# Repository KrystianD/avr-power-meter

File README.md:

avr-power-meter
======

Device for monitoring bidirectional DC energy usage using various shunt resistors. Designed to mount directly on the shunt.

This version targets 48 V systems (supports up to 85 V on the sensing side).

It is galvanically isolated from the power supply to prevent ground loops.

It communicates via the Modbus RTU protocol over an RS-485 interface.

The core components are the `INA228` sensor and an `ATtiny1626` microcontroller.

### History

See the v1 (test) version in [[v1]](https://github.com/KrystianD/avr-power-meter/tree/v1) branch. \
See the v2 (for 24V systems) version in [[v2]](https://github.com/KrystianD/avr-power-meter/tree/v2) branch.

# Board

<br/>

# Photos

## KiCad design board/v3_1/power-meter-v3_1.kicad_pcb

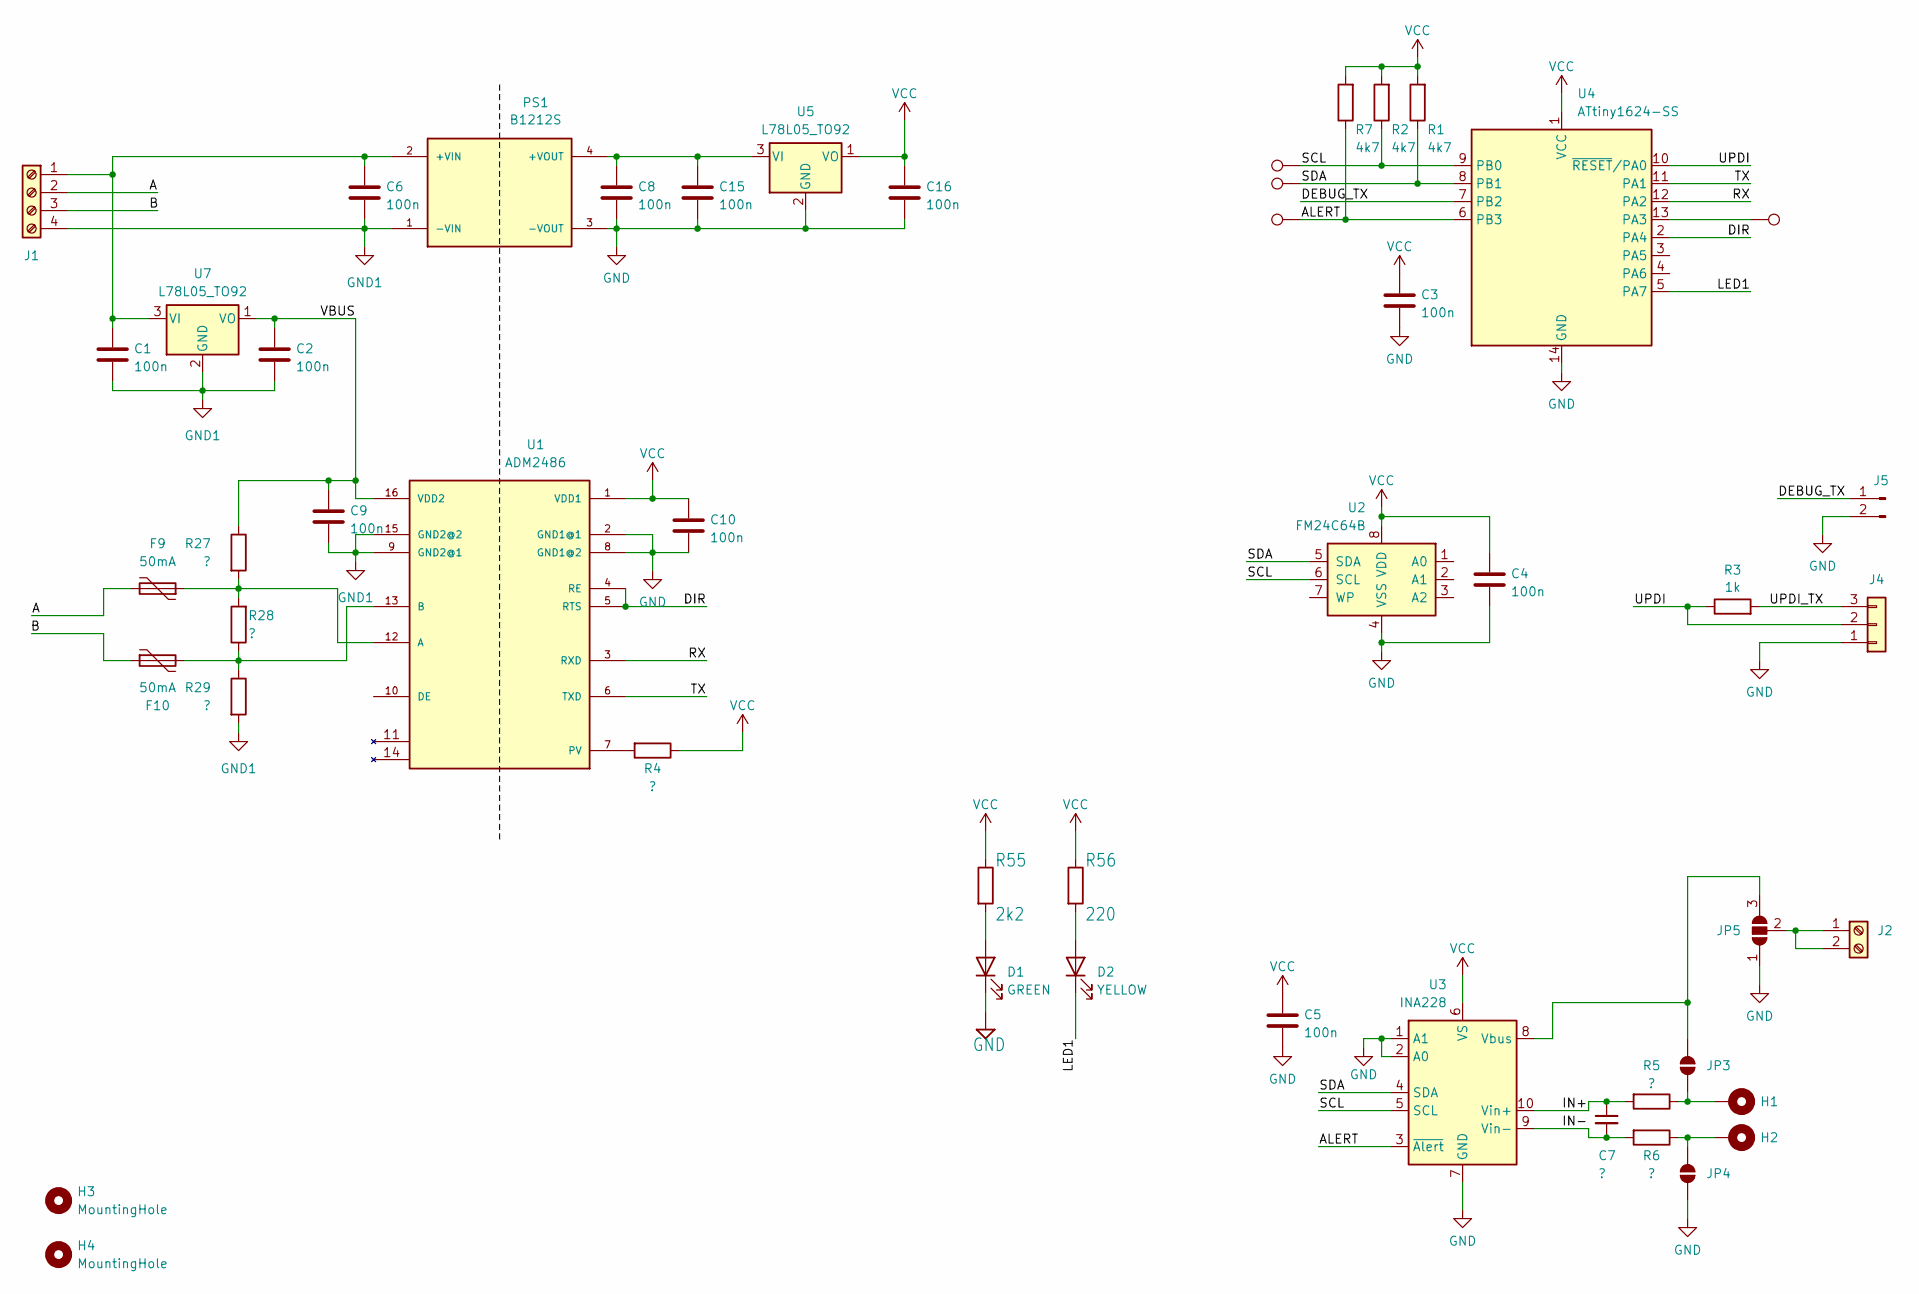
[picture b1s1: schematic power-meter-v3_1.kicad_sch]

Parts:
C1, C2, C3, C4, C5, C6, C8, C9, C10, C15, C16: 100n; C_0805_2012Metric_Pad1.18x1.45mm_HandSolder
C7: ?; C_0805_2012Metric_Pad1.18x1.45mm_HandSolder
D1: GREEN; LED_0805_2012Metric_Pad1.15x1.40mm_HandSolder
D2: YELLOW; LED_0805_2012Metric_Pad1.15x1.40mm_HandSolder
F9, F10: 50mA; R_1206_3216Metric_Pad1.30x1.75mm_HandSolder
H1, H2: MountingHole_Pad; M5-shunt-pad
H3, H4: MountingHole; MountingHole_3.2mm_M3
J1: Screw_Terminal_01x04; TerminalBlock_Phoenix_PT-1,5-4-3.5-H_1x04_P3.50mm_Horizontal
J2: Screw_Terminal_01x02; TerminalBlock_Phoenix_PT-1,5-2-3.5-H_1x02_P3.50mm_Horizontal
J4: Conn_01x03; PinHeader_1x03_P2.54mm_Vertical
J5: Conn_01x02_Pin; PinHeader_1x02_P2.54mm_Vertical
JP3, JP4: SolderJumper_2_Open; SolderJumper-2_P1.3mm_Open_RoundedPad1.0x1.5mm
JP5: SolderJumper_3_Open; SolderJumper-3_P1.3mm_Open_Pad1.0x1.5mm
PS1: B1212S; CONV_RO-0505S; PARTREV 3
R1: 4k7; R_1206_3216Metric_Pad1.30x1.75mm_HandSolder
R2, R7: 4k7; R_0805_2012Metric_Pad1.20x1.40mm_HandSolder
R3: 1k; R_0805_2012Metric_Pad1.20x1.40mm_HandSolder
R4, R5, R6, R27, R28, R29: ?; R_0805_2012Metric_Pad1.20x1.40mm_HandSolder
R55: 2k2; R_0805_2012Metric_Pad1.20x1.40mm_HandSolder
R56: 220; R_0805_2012Metric_Pad1.20x1.40mm_HandSolder
TP1, TP2, TP3, TP4: TestPoint; TestPoint_Pad_D1.5mm
U1: ADM2486; SOIC16R
U2: FM24C64B; SOIC-8_3.9x4.9mm_P1.27mm
U3: INA228; VSSOP-10_3x3mm_P0.5mm
U4: ATtiny1624-SS; SOIC-14_3.9x8.7mm_P1.27mm
U5, U7: L78L05_TO92; TO-92_Inline

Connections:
/A: F9.2, J1.2
/ALERT: R7.1, TP3.1 (1_1), U3.3 (~Alert), U4.6 (PB3)
/B: F10.1, J1.3
/DEBUG_TX: J5.1, U4.7 (PB2)
/DIR: U1.4 (RE), U1.5 (RTS), U4.2 (PA4)
/IN+: C7.1, R5.2, U3.10 (Vin+)
/IN-: C7.2, R6.2, U3.9 (Vin-)
/LED1: D2.1 (K), U4.5 (PA7)
/RX: U1.3 (RXD), U4.12 (PA2)
/SCL: R2.1, TP2.1 (1_1), U2.6 (SCL), U3.5 (SCL), U4.9 (PB0)
/SDA: R1.1, TP1.1 (1_1), U2.5 (SDA), U3.4 (SDA), U4.8 (PB1)
/TX: U1.6 (TXD), U4.11 (PA1)
/UPDI: J4.2, R3.1, U4.10 (~RESET/PA0)
/UPDI_TX: J4.3, R3.2
/VBUS: C2.2, C9.2, R27.1, U1.16 (VDD2), U7.1 (VO)
GND: C3.1, C4.1, C5.1, C8.1, C10.1, C15.1, C16.1, D1.1 (K), J4.1, J5.2, JP4.1 (A), JP5.1 (A), PS1.3 (-VOUT), U1.2 (GND1@1), U1.8 (GND1@2), U2.4 (VSS), U3.1 (A1), U3.2 (A0), U3.7 (GND), U4.14 (GND), U5.2 (GND)
GND1: C1.1, C2.1, C6.1, C9.1, J1.4, PS1.1 (-VIN), R29.2, U1.9 (GND2@1), U1.15 (GND2@2), U7.2 (GND)
unnamed: D1.2 (A), R55.2
unnamed: D2.2 (A), R56.2
unnamed: C1.2, C6.2, J1.1, PS1.2 (+VIN), U7.3 (VI)
unnamed: J2.1, J2.2, JP5.2 (C)
unnamed: H1.1 (1_1), JP3.1 (A), R5.1
unnamed: JP3.2 (B), JP5.3 (B), U3.8 (Vbus)
unnamed: H2.1 (1_1), JP4.2 (B), R6.1
unnamed: C8.2, C15.2, PS1.4 (+VOUT), U5.3 (VI)
unnamed: F9.1, R27.2, R28.2, U1.12 (A)
unnamed: F10.2, R28.1, R29.1, U1.13 (B)
unnamed: R4.2, U1.7 (PV)
unnamed: TP4.1 (1_1), U4.13 (PA3)
VCC: C3.2, C4.2, C5.2, C10.2, C16.2, R1.2, R2.2, R4.1, R7.2, R55.1, R56.1, U1.1 (VDD1), U2.8 (VDD), U3.6 (VS), U4.1 (VCC), U5.1 (VO)

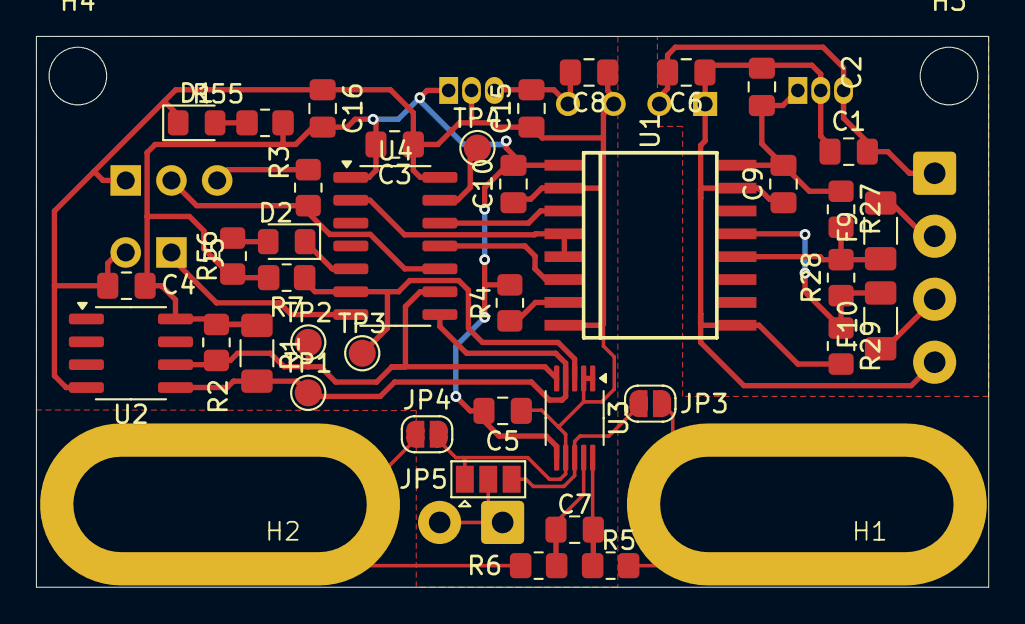
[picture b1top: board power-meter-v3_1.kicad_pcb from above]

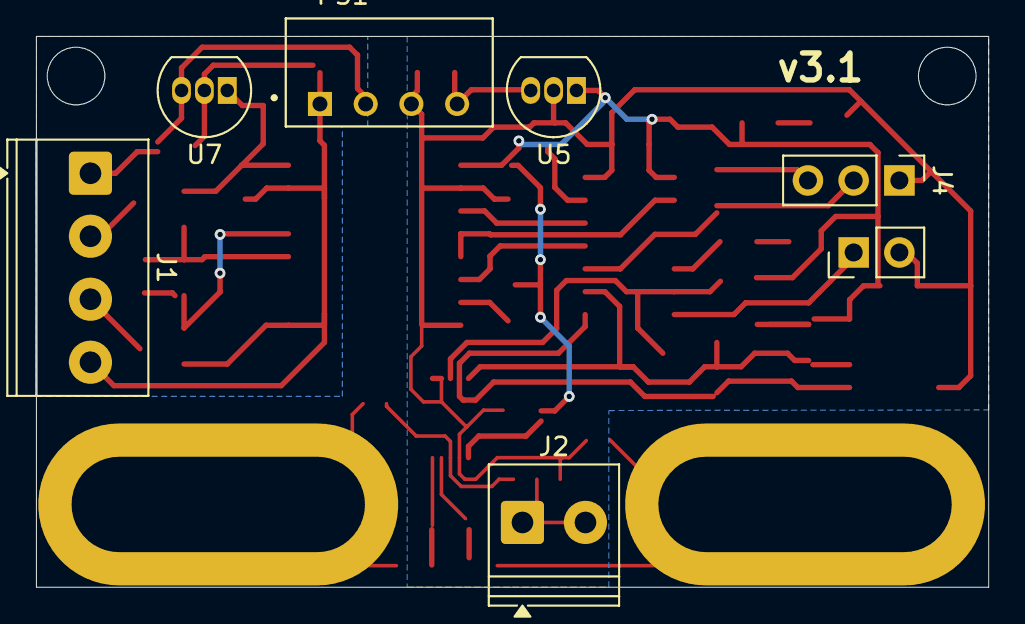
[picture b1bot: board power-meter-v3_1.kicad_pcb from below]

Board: 2 copper layers, 52.9 x 30.6 mm, 50 parts (7 on the bottom side), 30 nets.

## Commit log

2025-10-29 minor schematic updates
2026-06-28 register name fix
2026-06-28 updated ksystem
2026-06-28 board update
2026-06-28 reboot asynchronously to properly send modbus ack
2026-06-28 disabled stdio for production
2026-06-28 exposed mcu voltage as a modbus register
2026-06-28 updated dev_attiny
